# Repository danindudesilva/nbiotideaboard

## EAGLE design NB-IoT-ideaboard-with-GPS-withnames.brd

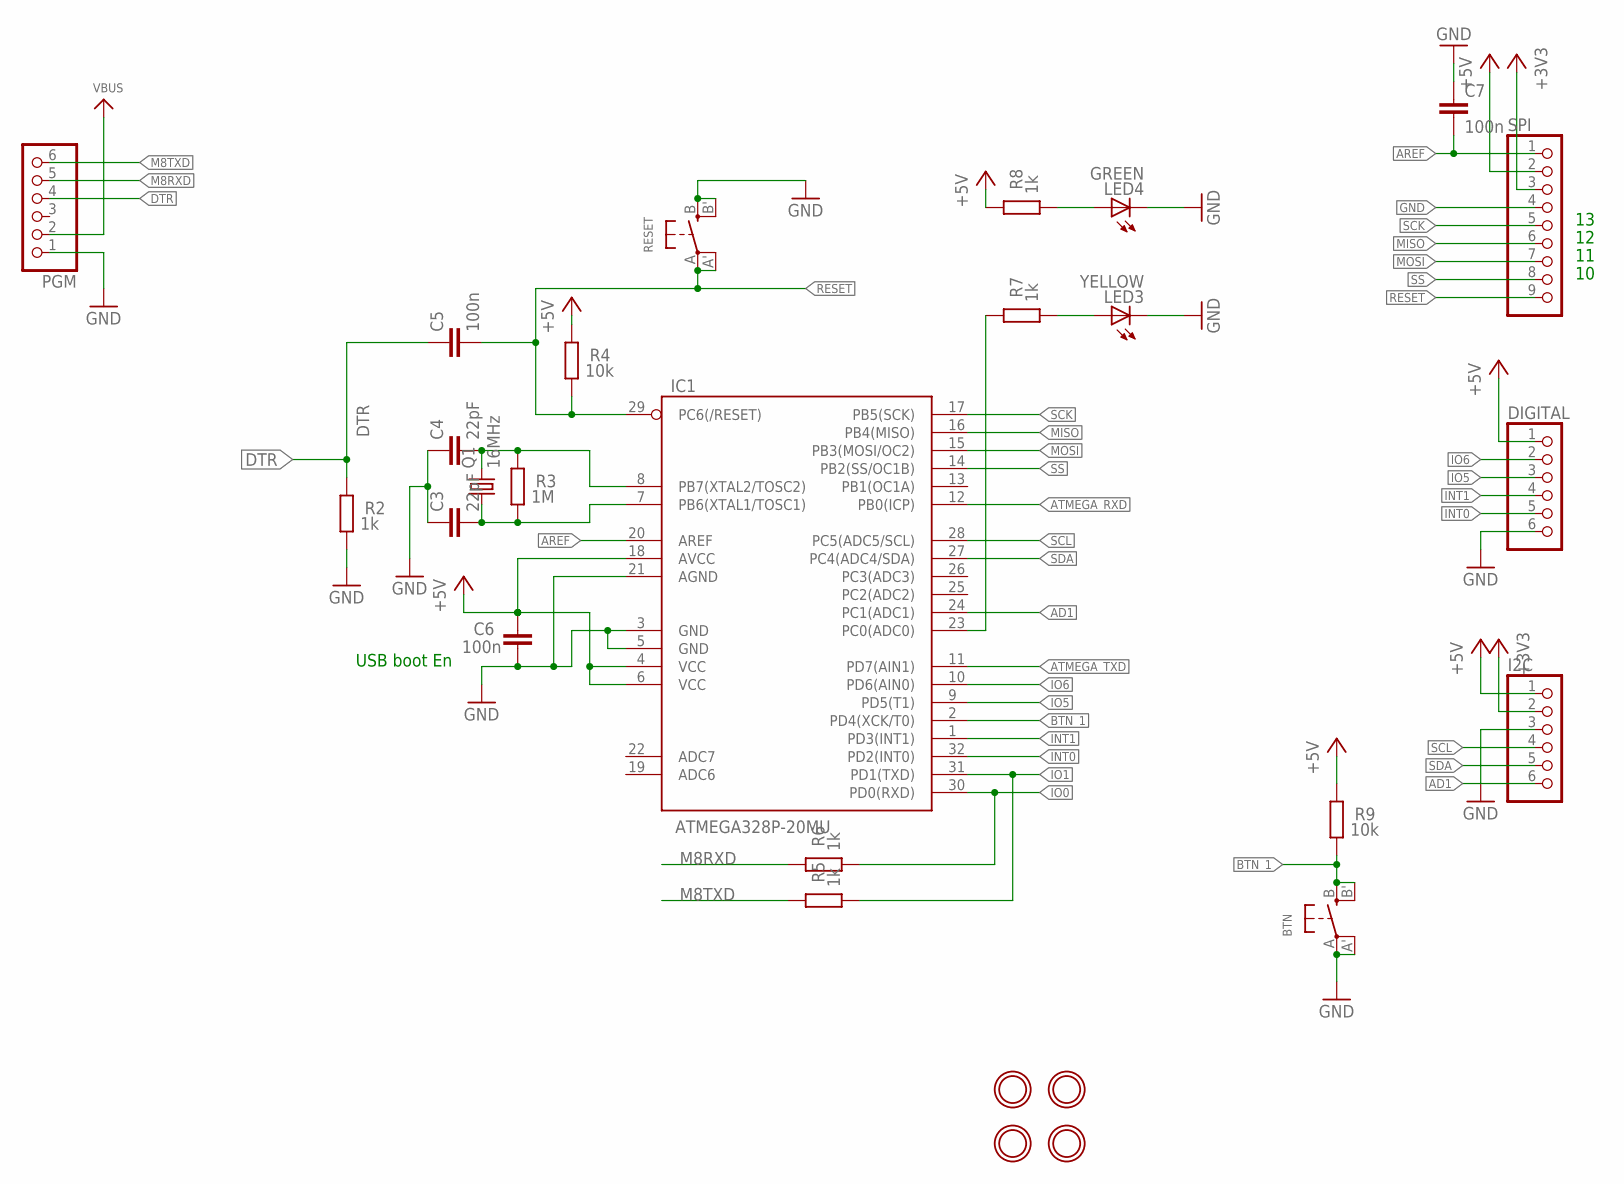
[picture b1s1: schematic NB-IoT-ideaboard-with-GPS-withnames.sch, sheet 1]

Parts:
$H1, $H2, $H3, $H4: MOUNTINGHOLE3.0THIN; MOUNTINGHOLE_3.0_PLATEDTHIN
BTN: SWITCH_TACT_SMT4.6X2.8; BTN_KMR2_4.6X2.8
C3, C4: 22pF; C0805
C5, C6, C7: 100n; C0805
DIGITAL: PINHD-1X6; 1X06
I2C: PINHD-1X6; 1X06
IC1: ATMEGA328P-20MU; TQFP32-08
LED3: YELLOW; CHIP-LED0805
LED4: GREEN; CHIP-LED0805
PGM: PINHD-1X6; 1X06
Q1: 16MHz; CTS406
R2, R5, R6, R7, R8: 1k; R0805
R3: 1M; R0805
R4, R9: 10k; R0805
RESET: SWITCH_TACT_SMT4.6X2.8; BTN_KMR2_4.6X2.8
SPI: PINHD-1X9; 1X09

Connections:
+3V3: I2C.2, SPI.3; also elsewhere on the board
+5V: C6.2, DIGITAL.1, I2C.1, IC1.4 (VCC), IC1.6 (VCC), IC1.18 (AVCC), R4.2, R8.2, R9.2, SPI.2; also elsewhere on the board
AD1: I2C.6, IC1.24 (PC1(ADC1))
AREF: C7.2, IC1.20 (AREF), SPI.1
ATMEGA_RXD: IC1.12 (PB0(ICP)); also elsewhere on the board
ATMEGA_TXD: IC1.11 (PD7(AIN1)); also elsewhere on the board
BTN_1: BTN.B (S), BTN.B' (S1), IC1.2 (PD4(XCK/T0)), R9.1
DTR: C5.1, PGM.4, R2.2
GND: BTN.A, BTN.A' (P1), C3.1, C4.1, C6.1, C7.1, DIGITAL.6, I2C.3, IC1.3 (GND), IC1.5 (GND), IC1.21 (AGND), LED3.C, LED4.C, PGM.1, R2.1, RESET.B (S), RESET.B' (S1), SPI.4; also elsewhere on the board
INT0: DIGITAL.5, IC1.32 (PD2(INT0))
INT1: DIGITAL.4, IC1.1 (PD3(INT1))
IO0: IC1.30 (PD0(RXD)), R6.1
IO1: IC1.31 (PD1(TXD)), R5.1
IO5: DIGITAL.3, IC1.9 (PD5(T1))
IO6: DIGITAL.2, IC1.10 (PD6(AIN0))
M8RXD: PGM.5, R6.2
M8TXD: PGM.6, R5.2
MISO: IC1.16 (PB4(MISO)), SPI.6
MOSI: IC1.15 (PB3(MOSI/OC2)), SPI.7; also elsewhere on the board
unnamed: LED3.A, R7.1
unnamed: LED4.A, R8.1
unnamed: IC1.23 (PC0(ADC0)), R7.2
RESET: C5.2, IC1.29 (PC6(/RESET)), R4.1, RESET.A, RESET.A' (P1), SPI.9
SCK: IC1.17 (PB5(SCK)), SPI.5; also elsewhere on the board
SCL: I2C.4, IC1.28 (PC5(ADC5/SCL))
SDA: I2C.5, IC1.27 (PC4(ADC4/SDA))
SS: IC1.14 (PB2(SS/OC1B)), SPI.8
VBUS: PGM.2; also elsewhere on the board
XTAL1: C3.2, IC1.7 (PB6(XTAL1/TOSC1)), Q1.1, R3.1
XTAL2: C4.2, IC1.8 (PB7(XTAL2/TOSC2)), Q1.3 (2), R3.2

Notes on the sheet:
USB boot En

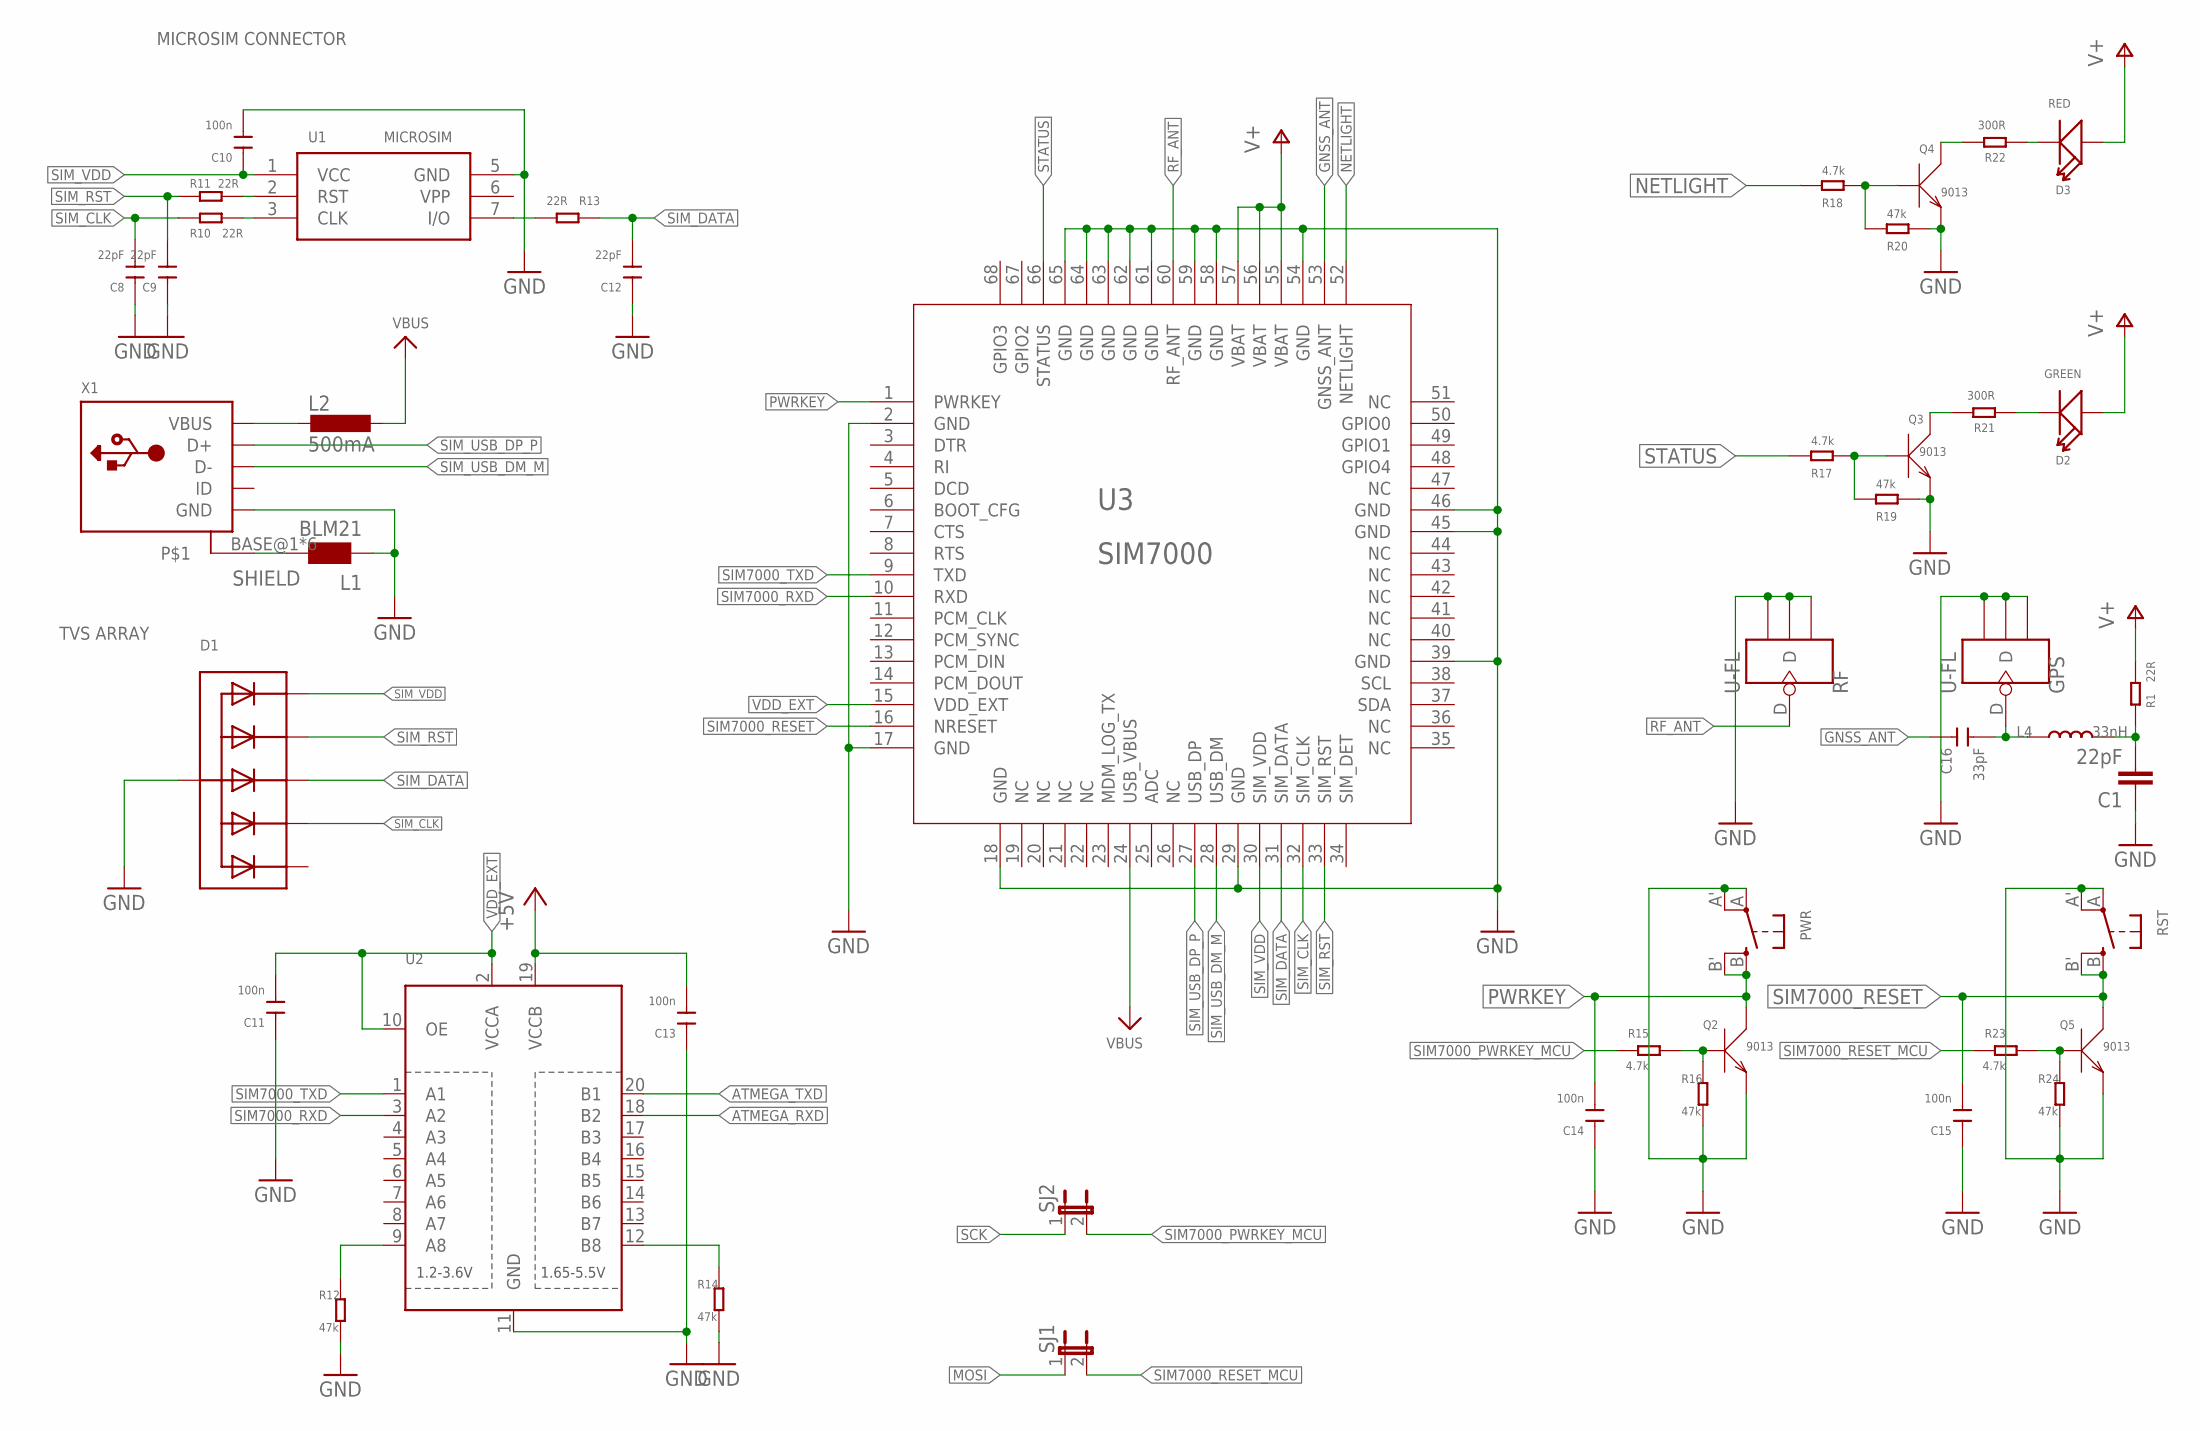
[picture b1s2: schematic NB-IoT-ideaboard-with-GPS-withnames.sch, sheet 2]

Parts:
C1: 22pF; C0805
C8, C9, C12: 22pF; 0805
C10, C11, C13, C14, C15: 100n; 0805
C16: 33pF; 0805
D1: TVSARRAY_5LANE; SOT363
D2: GREEN; LED-0805
D3: RED; LED-0805
GPS: U-FL; 4P-U-FL
L1: BLM21; 0805
L2: 500mA; L1812
L4: 33nH; L0805
PWR: SWITCH_TACT_SMT4.6X2.8; BTN_KMR2_4.6X2.8
Q2, Q3, Q4, Q5: 9013; SOT23
R1, R10, R11, R13: 22R; 0805
R12, R14, R16, R19, R20, R24: 47k; 0805
R15, R17, R18, R23: 4.7k; 0805
R21, R22: 300R; 0805
RF: U-FL; 4P-U-FL
RST: SWITCH_TACT_SMT4.6X2.8; BTN_KMR2_4.6X2.8
SJ1, SJ2: SPARKFUN-PASSIVES_JUMPER-PTH-2-NC; SPARKFUN-PASSIVES_PTH-JUMPER-NC_BOTTOM_NO_SILK
U1: MICROSIM
U2: TXB0108PWR; TSSOP20
U3: SIM7000
X1: USB_MICRO_20329_V2; 4UCONN_20329_V2

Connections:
+5V: C13.2, U2.19 (VCCB); also elsewhere on the board
ATMEGA_RXD: U2.18 (B2); also elsewhere on the board
ATMEGA_TXD: U2.20 (B1); also elsewhere on the board
GND: C1.1, C8.1, C9.1, C10.2, C11.1, C12.1, C13.1, C14.1, C15.1, D1.2 (A), GPS.GND1, GPS.GND2, GPS.GND3, L1.1, PWR.A, PWR.A' (P1), Q2.2 (E), Q3.2 (E), Q4.2 (E), Q5.2 (E), R12.2, R14.2, R16.2, R19.2, R20.2, R24.2, RF.GND1, RF.GND2, RF.GND3, RST.A, RST.A' (P1), U1.5 (GND), U2.11 (GND), U3.2 (GND), U3.17 (GND), U3.18 (GND), U3.29 (GND), U3.39 (GND), U3.45 (GND), U3.46 (GND), U3.54 (GND), U3.58 (GND), U3.59 (GND), U3.61 (GND), U3.62 (GND), U3.63 (GND), U3.64 (GND), U3.65 (GND), X1.GND; also elsewhere on the board
GNSS_ANT: C16.2, U3.53 (GNSS_ANT)
GPIO2: U3.67 (GPIO2)
GPIO3: U3.68 (GPIO3)
MOSI: SJ1.1; also elsewhere on the board
unnamed: Q3.3 (C), R21.2
unnamed: D2.-, R21.1
unnamed: Q3.1 (B), R17.2, R19.1
unnamed: R13.2, U1.7 (I/O)
unnamed: R10.1, U1.3 (CLK)
unnamed: R11.1, U1.2 (RST)
unnamed: Q5.1 (B), R23.2, R24.1
unnamed: L2.2, X1.VBUS
unnamed: Q4.3 (C), R22.2
unnamed: D3.-, R22.1
unnamed: Q4.1 (B), R18.2, R20.1
unnamed: C16.1, GPS.D, L4.1
unnamed: R12.1, U2.9 (A8)
unnamed: R14.1, U2.12 (B8)
unnamed: C1.2, L4.2, R1.2
unnamed: Q2.1 (B), R15.2, R16.1
NETLIGHT: R18.1, U3.52 (NETLIGHT)
PWRKEY: C14.2, PWR.B (S), PWR.B' (S1), Q2.3 (C), U3.1 (PWRKEY)
RF_ANT: RF.D, U3.60 (RF_ANT)
SCK: SJ2.1; also elsewhere on the board
SHIELD: L1.2, X1.BASE@1, X1.BASE@2, X1.SPRT@1, X1.SPRT@2, X1.SPRT@3, X1.SPRT@4
SIM7000_PWRKEY_MCU: R15.1, SJ2.2
SIM7000_RESET: C15.2, Q5.3 (C), RST.B (S), RST.B' (S1), U3.16 (NRESET)
SIM7000_RESET_MCU: R23.1, SJ1.2
SIM7000_RXD: U2.3 (A2), U3.10 (RXD)
SIM7000_TXD: U2.1 (A1), U3.9 (TXD)
SIM_CLK: C8.2, D1.5 (C4), R10.2, U3.32 (SIM_CLK)
SIM_DATA: C12.2, D1.4 (C3), R13.1, U3.31 (SIM_DATA)
SIM_RST: C9.2, D1.3 (C2), R11.2, U3.33 (SIM_RST)
SIM_USB_DM_M: U3.28 (USB_DM), X1.D-
SIM_USB_DP_P: U3.27 (USB_DP), X1.D+
SIM_VDD: C10.1, D1.1 (C1), U1.1 (VCC), U3.30 (SIM_VDD)
STATUS: R17.1, U3.66 (STATUS)
V+: D2.+, D3.+, R1.1, U3.55 (VBAT), U3.56 (VBAT), U3.57 (VBAT); also elsewhere on the board
VBUS: L2.1, U3.24 (USB_VBUS); also elsewhere on the board
VDD_EXT: C11.2, U2.2 (VCCA), U2.10 (OE), U3.15 (VDD_EXT)

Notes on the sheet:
TVS ARRAY
MICROSIM CONNECTOR

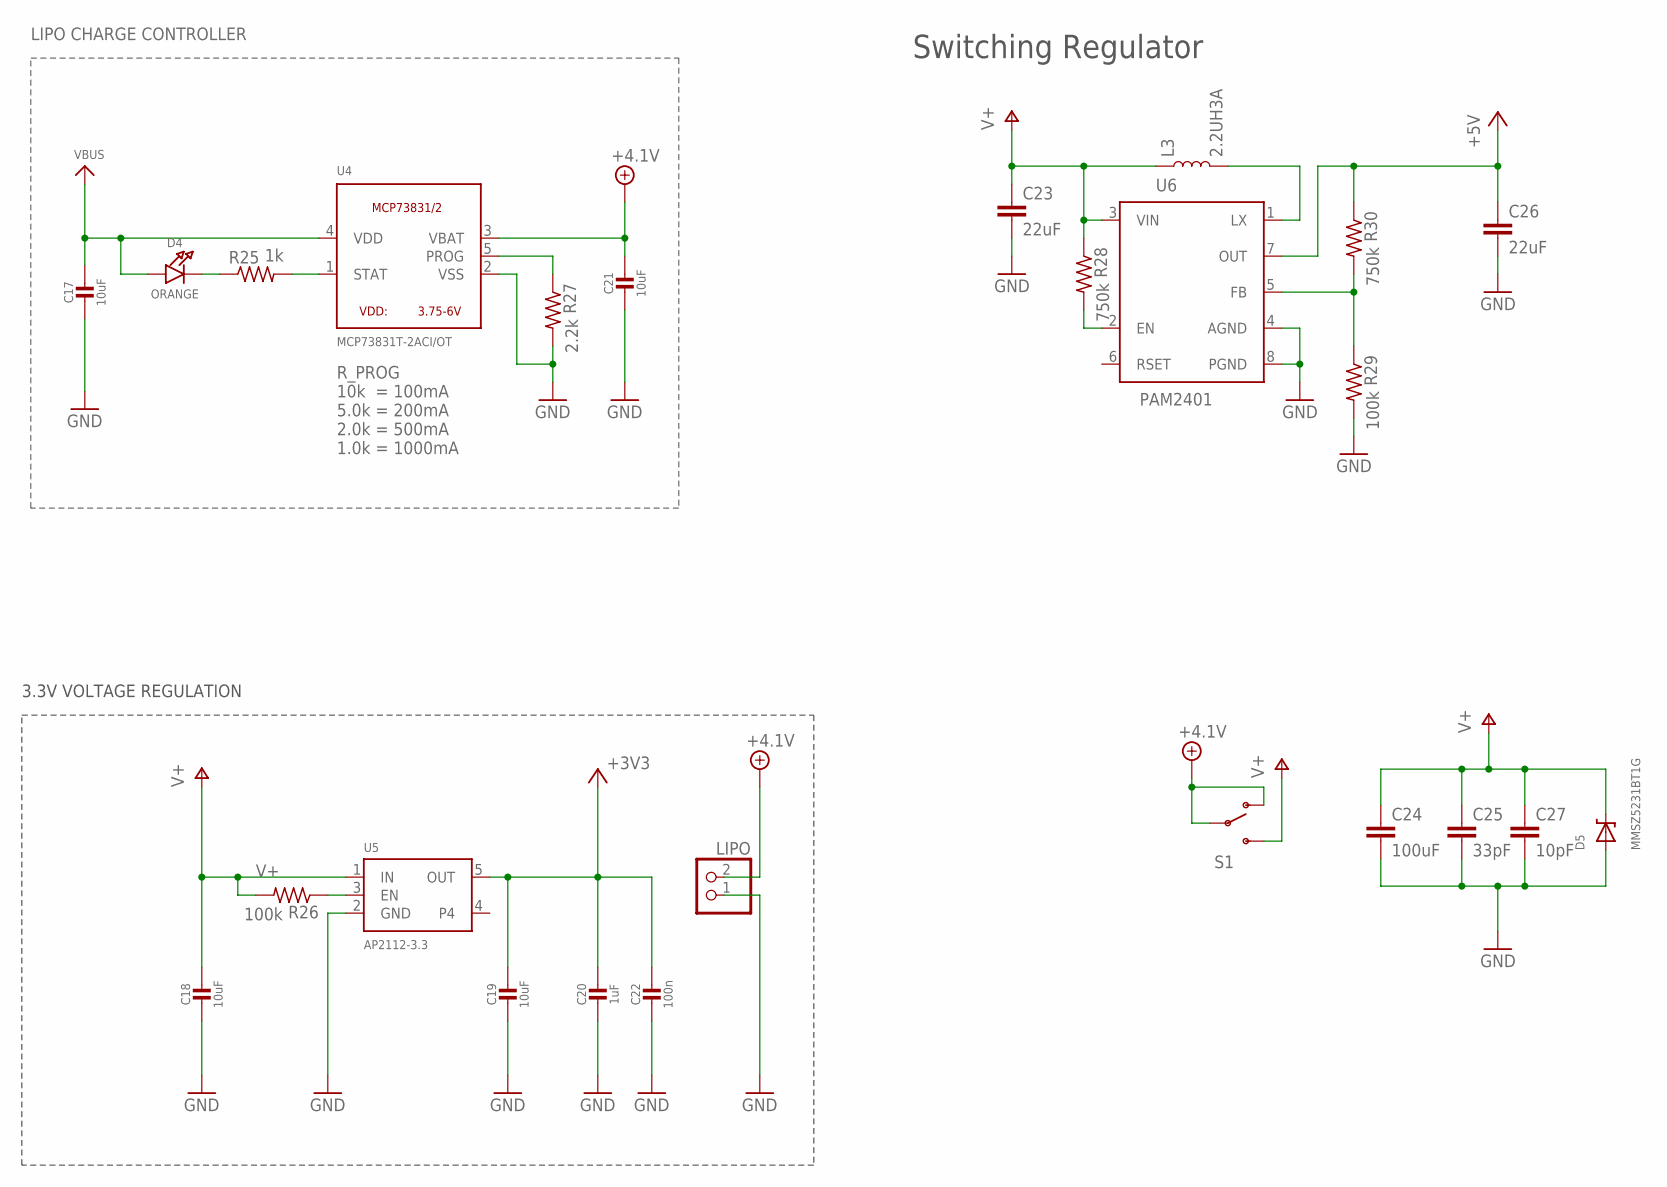
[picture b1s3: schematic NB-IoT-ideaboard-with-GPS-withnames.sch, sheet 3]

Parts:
C17, C21: 10uF; _0805
C18, C19: 10uF; _0805MP
C20: 1uF; _0805MP
C22: 100n; _0805MP
C23, C26: 22uF; 0805
C24: 100uF; 1210
C25: 33pF; 0805
C27: 10pF; 0805
D4: ORANGE; CHIPLED_0805
D5: MMSZ5231BT1G; SOD-123
L3: 2.2UH3A; INDUCTOR_4X4MM
LIPO: JST_2PIN-SMT; JST-PH-2-SMT
R25: 1k; M0805
R26, R29: 100k; M0805
R27: 2.2k; M0805
R28, R30: 750k; M0805
S1: SWITCH-SPDT-SMD-A; SWITCH-SPST-SMD-A
U4: MCP73831T-2ACI/OT; SOT23-5
U5: AP2112-3.3; SOT23-5
U6: PAM2401; MSOP8

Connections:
+3V3: C19.1, C20.1, C22.1, U5.5 (OUT); also elsewhere on the board
+4.1V: C21.1, LIPO.2 (1), S1.1 (O), S1.2, U4.3 (VBAT)
+5V: C26.1, R30.1, U6.7 (OUT); also elsewhere on the board
EN: R28.2, U6.2 (EN)
GND: C17.2, C18.2, C19.2, C20.2, C21.2, C22.2, C23.2, C24.2, C25.2, C26.2, C27.2, D5.A, LIPO.1 (2), R27.2, R29.2, U4.2 (VSS), U5.2 (GND), U6.4 (AGND), U6.8 (PGND); also elsewhere on the board
unnamed: R26.1, U5.3 (EN)
unnamed: D4.C, R25.1
unnamed: R25.2, U4.1 (STAT)
unnamed: R27.1, U4.5 (PROG)
unnamed: R29.1, R30.2, U6.5 (FB)
unnamed: L3.P$2 (2), U6.1 (LX)
V+: C18.1, C23.1, C24.1, C25.1, C27.1, D5.C, L3.P$1 (1), R26.2, R28.1, S1.3 (S), U5.1 (IN), U6.3 (VIN); also elsewhere on the board
VBUS: C17.1, D4.A, U4.4 (VDD); also elsewhere on the board

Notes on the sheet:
3.3V VOLTAGE REGULATION
R_PROG 10k = 100mA 5.0k = 200mA 2.0k = 500mA 1.0k = 1000mA
LIPO CHARGE CONTROLLER
Switching Regulator

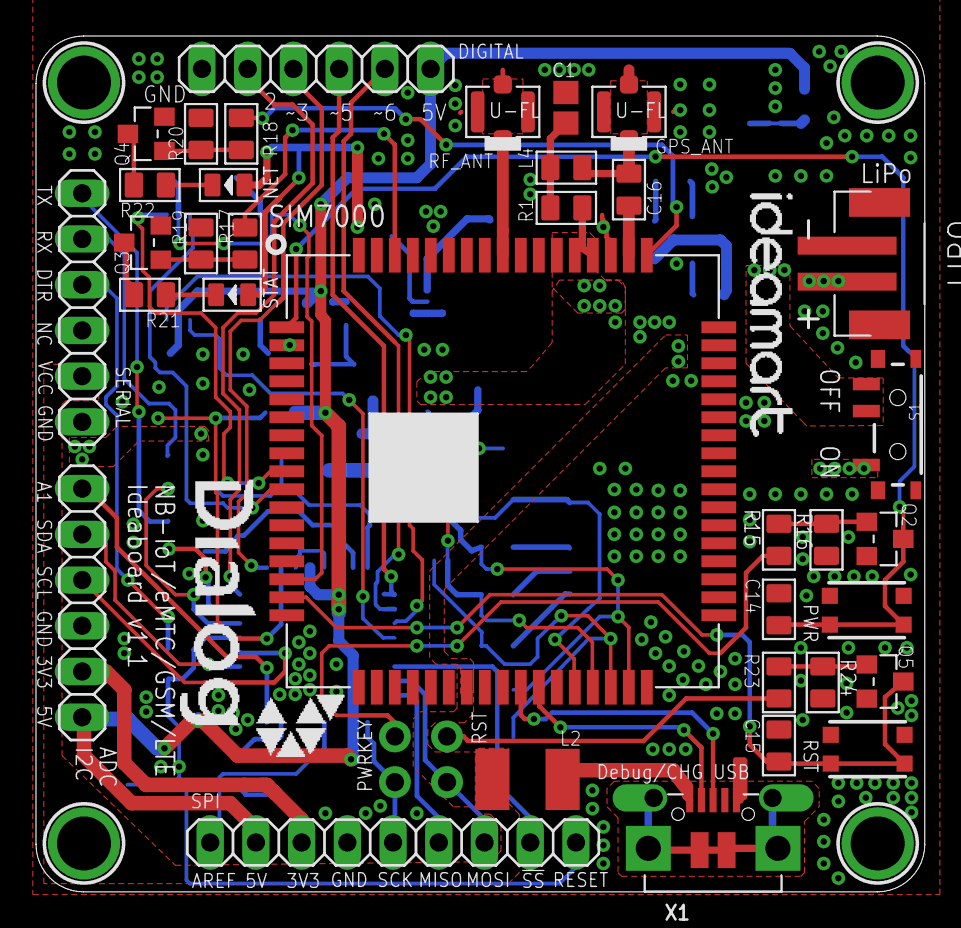
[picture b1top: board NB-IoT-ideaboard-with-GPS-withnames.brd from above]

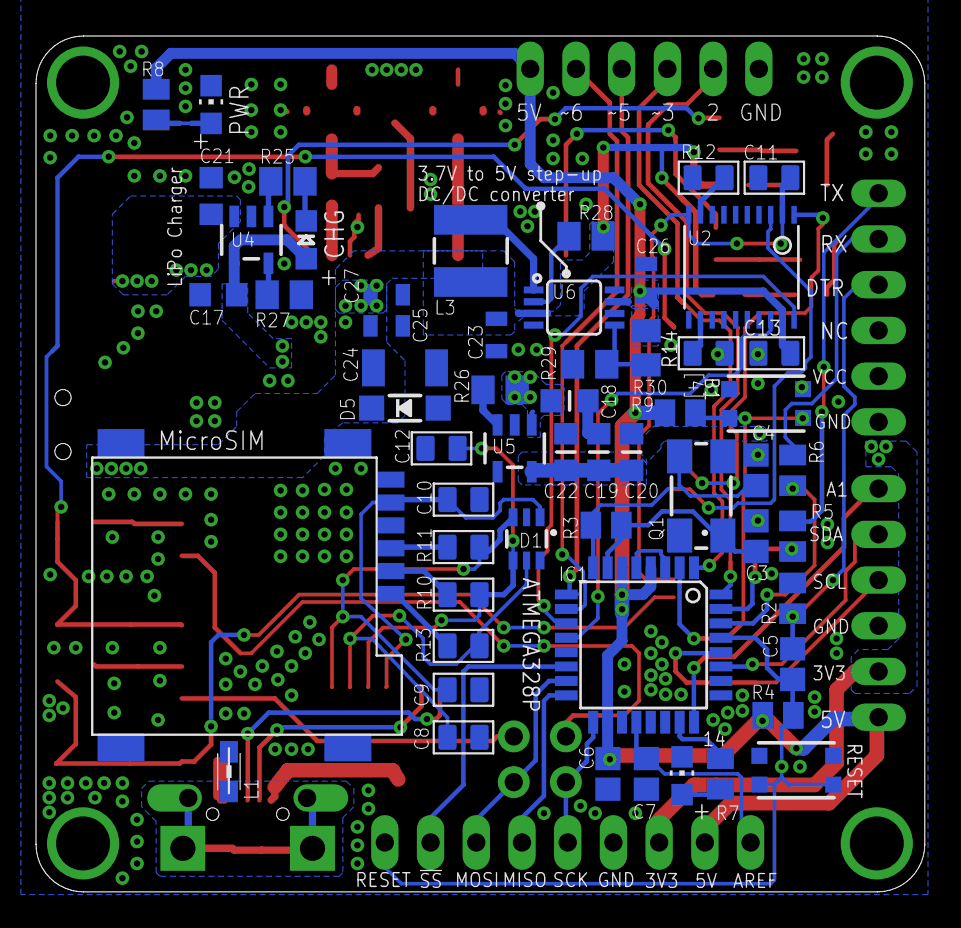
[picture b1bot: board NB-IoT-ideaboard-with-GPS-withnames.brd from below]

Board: 2 copper layers, 49.4 x 47.5 mm, 98 parts (57 on the bottom side), 73 nets.

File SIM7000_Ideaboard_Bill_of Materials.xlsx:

Qty | Value | Device | Package | Parts | Description | BOM | MF | MPN | OC_FARNELL | OC_NEWARK | PROD_ID | VALUE
1 | LiPo | JST_2PIN-SMT | JST-PH-2-SMT | LIPO | JST 2-Pin Connectors of various flavors
3 | Digital, I2C, PGM | PINHD-1X6 | 1X06 | DIGITAL, I2C, PGM | PIN HEADER
1 | SPI | PINHD-1X9 | 1X09 | SPI | PIN HEADER
1 | On off | SWITCH-SPDT-SMD-A | SWITCH-SPST-SMD-A | S1 | SPDT Switch |  |  |  |  |  | SWCH-10651
4 | Push button | SWITCH_TACT_SMT4.6X2.8 | BTN_KMR2_4.6X2.8 | BTN, PWR, RESET, RST | SMT Tact Switches
1 | SMF15C | TVSARRAY_5LANE | SOT363 | D1 | Voltage Transient Suppressor Array
1 | Level shifter | TXB0108PWR | TSSOP20 | U2 | 8-Bit Bi-Directional Level Shifter
1 | SIM7000 USB | USB_MICRO_20329_V2 | 4UCONN_20329_V2 | X1 | USB Connectors
2 | 100k | R-US_M0805 | M0805 | R26, R29 | RESISTOR, American symbol
5 | 100n | C-0805 | 805 | C10, C11, C13, C14, C15 | Ceramic Capacitors
3 | 100n | C-EUC0805 | C0805 | C5, C6, C7 | CAPACITOR, European symbol
1 | 100n | CAP_CERAMIC_0805MP | _0805MP | C22 | Ceramic Capacitors
1 | 100uF | 22UF-1210-16V-20% | 1210 | C24 | 22ｵF ceramic capacitors
2 | 10k | R-EU_R0805 | R0805 | R4, R9 | RESISTOR, European symbol
1 | 10pF | 22UF-0805-6.3V-20% | 805 | C27 | 22ｵF ceramic capacitors |  |  |  |  |  | CAP-08402 | 22uF
2 | 10uF | CAP_CERAMIC_0805 | _0805 | C17, C21 | Ceramic Capacitors
2 | 10uF | CAP_CERAMIC_0805MP | _0805MP | C18, C19 | Ceramic Capacitors
1 | 16MHz | CRYSTALCTS406 | CTS406 | Q1 | CRYSTAL |  |  |  | unknown | unknown
1 | 1M | R-EU_R0805 | R0805 | R3 | RESISTOR, European symbol
5 | 1k | R-EU_R0805 | R0805 | R2, R5, R6, R7, R8 | RESISTOR, European symbol
1 | 1k | R-US_M0805 | M0805 | R25 | RESISTOR, American symbol
1 | 1uF | CAP_CERAMIC_0805MP | _0805MP | C20 | Ceramic Capacitors
1 | 2.2UH3A | INDUCTOR-IFSC1515AHER2R2M01 | INDUCTOR_4X4MM | L3 | Inductors |  |  |  |  |  | NDUC-13770 | 2.2UH3A
1 | 2.2k | R-US_M0805 | M0805 | R27 | RESISTOR, American symbol
4 | 22R | R-0805 | 805 | R1, R10, R11, R13
3 | 22pF | C-0805 | 805 | C8, C9, C12 | Ceramic Capacitors
3 | 22pF | C-EUC0805 | C0805 | C1, C3, C4 | CAPACITOR, European symbol
2 | 22uF | 22UF-0805-6.3V-20% | 805 | C23, C26 | 22ｵF ceramic capacitors |  |  |  |  |  | CAP-08402 | 22uF
2 | 300R | R-0805 | 805 | R21, R22
1 | 33nH | L0805 | L0805 | L4 | Inductor |  |  | RK73B2ATTDD104J
1 | 33pF | 22UF-0805-6.3V-20% | 805 | C25 | 22ｵF ceramic capacitors |  |  |  |  |  | CAP-08402 | 22uF
1 | 33pF | C-0805 | 805 | C16 | Ceramic Capacitors
4 | 4.7k | R-0805 | 805 | R15, R17, R18, R23
6 | 47k | R-0805 | 805 | R12, R14, R16, R19, R20, R24
1 | 500mA | L-EUL1812 | L1812 | L2 | INDUCTOR, European symbol
2 | 750k | R-US_M0805 | M0805 | R28, R30 | RESISTOR, American symbol
4 | s9013 | TRANSISTOR-NPN-SOT23 | SOT23 | Q2, Q3, Q4, Q5 | NPN audion
1 | AP2112-3.3 | VREG_SOT23-5 | SOT23-5 | U5 | SOT23-5 Fixed Voltage Regulators
1 | ATMEGA328P-20MU | MEGA8-AI | TQFP32-08 | IC1 | MICROCONTROLLER
1 | BLM21 | WE-CBF_0805 | 805 | L1 | SMD EMI Suppression Ferrite Beads
1 | GREEN | LED'0805' | LED-0805 | D2
1 | GREEN | LEDCHIP-LED0805 | CHIP-LED0805 | LED4 | LED
1 | MCP73831T-2ACI/OT | MCP73831/2 | SOT23-5 | U4 | MCP73831/2 LIPO Charger
1 | MICROSIM | MICROSIM | MICROSIM | U1
1 | MMSZ5231BT1G | DIODE-ZENERSOD123 | SOD-123 | D5 | Zener Diode
4 | MOUNTINGHOLE3.0THIN | MOUNTINGHOLE3.0THIN | MOUNTINGHOLE_3.0_PLATEDTHIN | $H1, $H2, $H3, $H4 | Mounting Hole | EXCLUDE
1 | ORANGE | LED0805 | CHIPLED_0805 | D4 | LED
1 | PAM2401 | PAM2401 | MSOP8 | U6 | PAM2401 - Boost PMIC |  |  |  |  |  | IC-13769 | PAM2401
1 | RED | LED'0805' | LED-0805 | D3
1 | SIM7000 | SIM7000 | SIM7000 | U3
2 | SPARKFUN-PASSIVES_JUMPER-PTH-2-NC | SPARKFUN-PASSIVES_JUMPER-PTH-2-NC | SPARKFUN-PASSIVES_PTH-JUMPER-NC_BOTTOM_NO_SILK | SJ1, SJ2
2 | U-FL | ANTENNA-U-FL | 4P-U-FL | GPS, RF
1 | YELLOW | LEDCHIP-LED0805 | CHIP-LED0805 | LED3 | LED

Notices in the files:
parts and their libraries:
SparkFun-Capacitors: Licensing: CC v3.0 Share-Alike You are welcome to use this library for commercial purposes.
SparkFun-Coils: Licensing: Creative Commons ShareAlike 4.0 International - https://creativecommons.org/licenses/by-sa/4.0
